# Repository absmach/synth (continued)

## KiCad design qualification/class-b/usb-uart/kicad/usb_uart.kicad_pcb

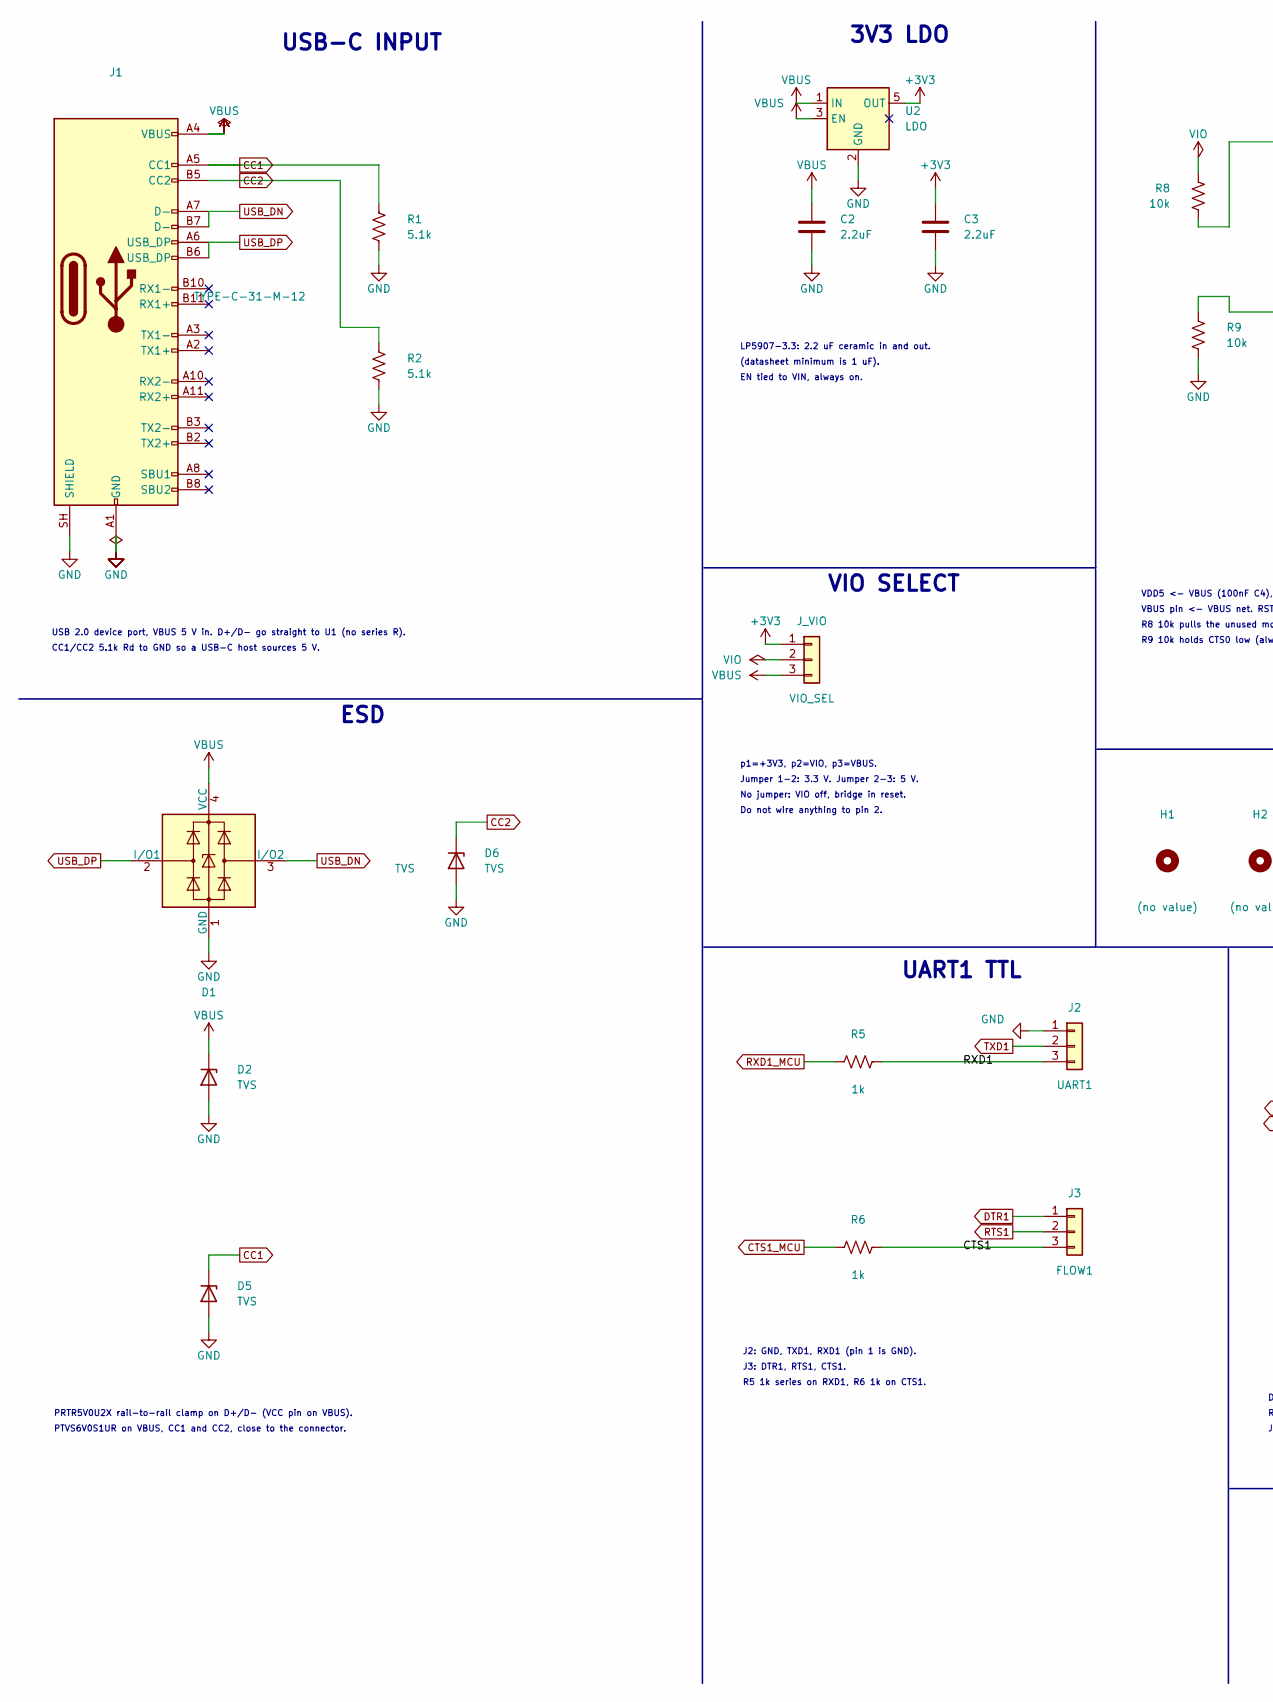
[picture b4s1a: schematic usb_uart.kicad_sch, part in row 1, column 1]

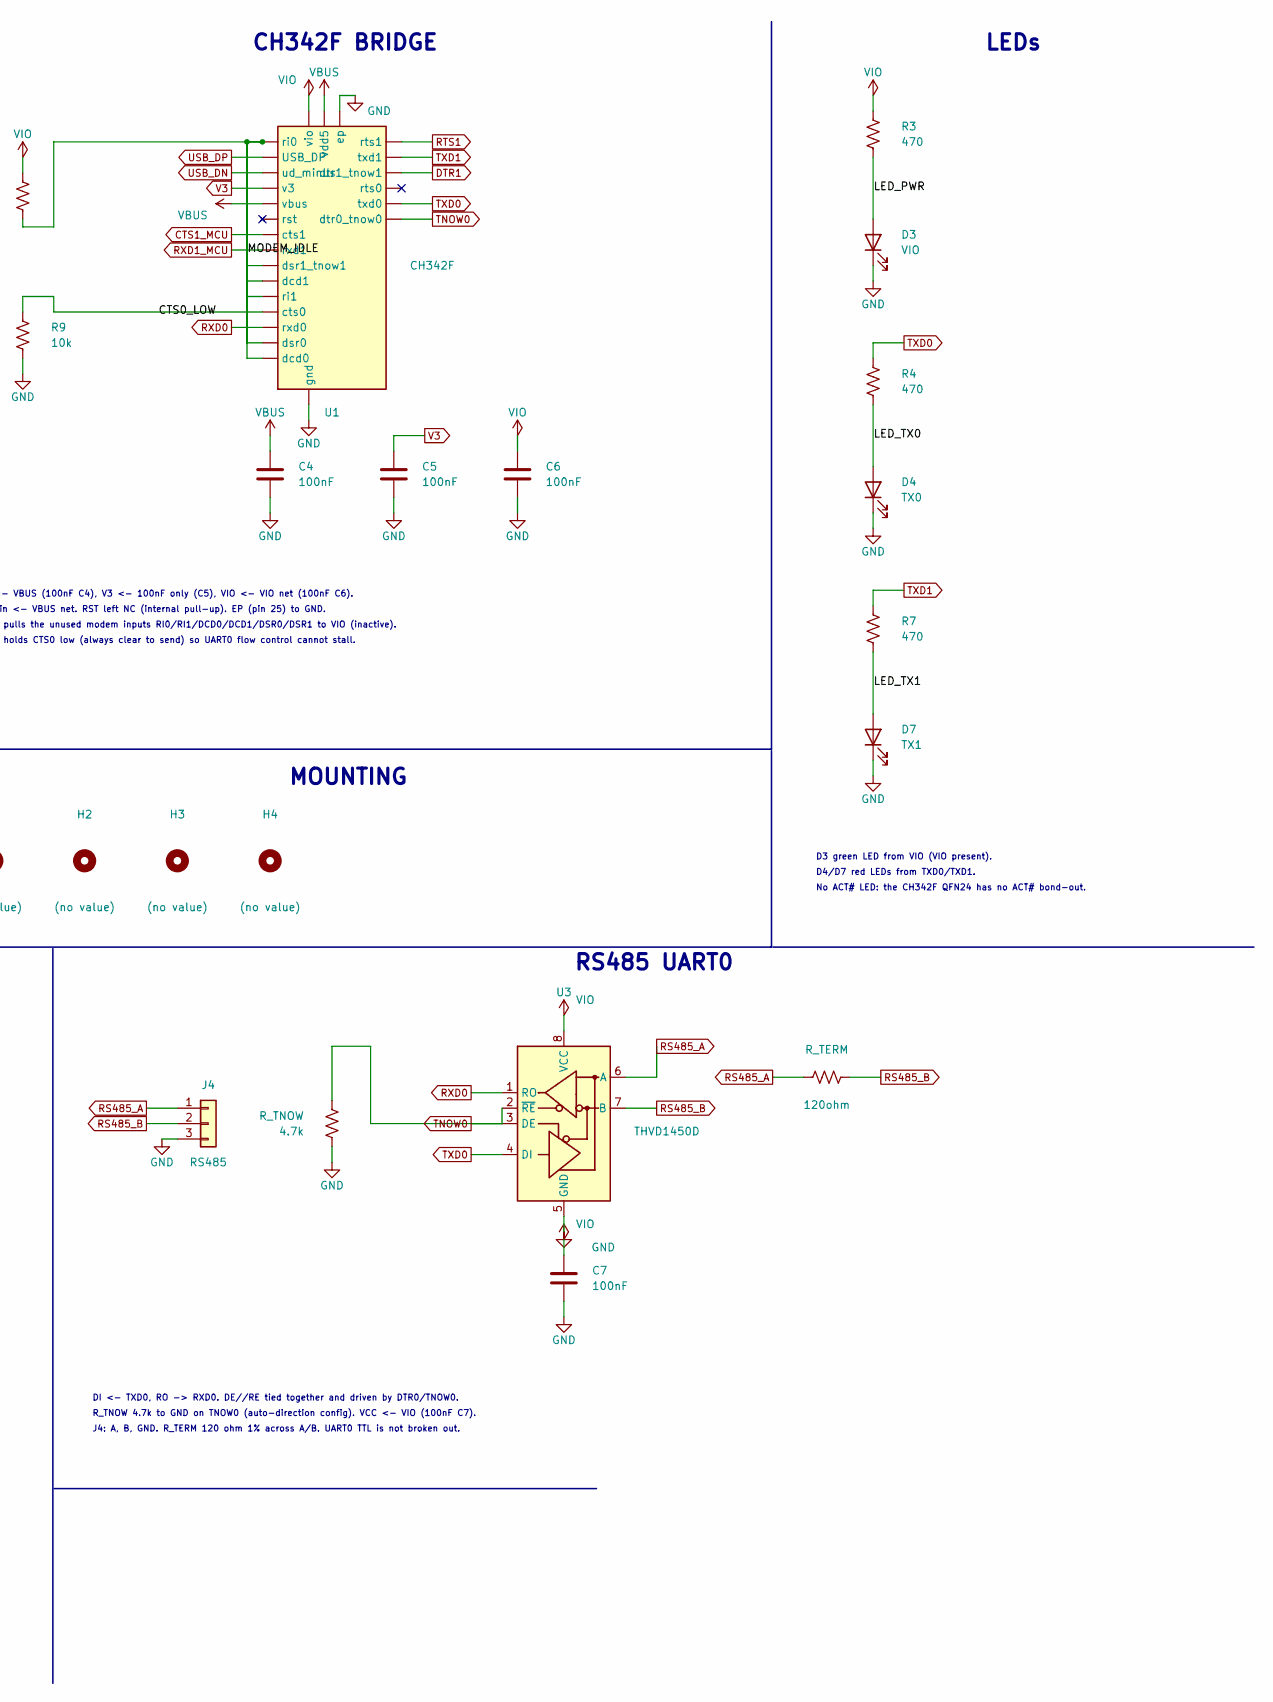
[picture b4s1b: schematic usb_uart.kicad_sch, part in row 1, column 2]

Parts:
C2, C3: 2.2uF; C_0603_1608Metric; Voltage 16V
C4, C5, C6, C7: 100nF; C_0603_1608Metric; Voltage 16V
D1: TVS; SOT-143; MPN PRTR5V0U2X
D2, D5, D6: TVS; Nexperia_CFP3_SOD-123W; MPN PTVS6V0S1UR
D3: VIO; LED_0603_1608Metric; MPN LTST-C190KGKT
D4: TX0; LED_0603_1608Metric; MPN LTST-C190KRKT
D7: TX1; LED_0603_1608Metric; MPN LTST-C190KRKT
H1, H2, H3, H4: (no value); MountingHole_2.5mm
J1: TYPE-C-31-M-12; USB_C_Receptacle_HRO_TYPE-C-31-M-12; MPN TYPE-C-31-M-12; LCSC C165948
J2: UART1; PinHeader_1x03_P2.54mm_Vertical
J3: FLOW1; PinHeader_1x03_P2.54mm_Vertical
J4: RS485; PinHeader_1x03_P2.54mm_Vertical
J_VIO: VIO_SEL; PinHeader_1x03_P2.54mm_Vertical
R1, R2: 5.1k; R_0603_1608Metric
R3, R4, R7: 470; R_0603_1608Metric
R5, R6: 1k; R_0603_1608Metric
R8, R9: 10k; R_0603_1608Metric
R_TERM: 120ohm; R_0603_1608Metric; Tolerance 1%
R_TNOW: 4.7k; R_0603_1608Metric; Tolerance 1%
U1: CH342F; QFN-24-1EP_4x4mm_P0.5mm_EP2.6x2.6mm; MPN CH342F; LCSC C2841530
U2: LDO; SOT-23-5; MPN LP5907MFX-3.3; LCSC C83437
U3: THVD1450D; SOIC-8_3.9x4.9mm_P1.27mm; MPN THVD1450D; LCSC C2671361

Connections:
+3V3: C3.1, J_VIO.1, U2.5 (OUT)
CC1: D5.1 (K), J1.A5 (CC1), R1.1
CC2: D6.1 (K), J1.B5 (CC2), R2.1
CTS0_LOW: R9.1, U1.18 (cts0)
CTS1: J3.3, R6.2
CTS1_MCU: R6.1, U1.10 (cts1)
DTR1: J3.1, U1.15 (dtr1_tnow1)
GND: C2.2, C3.2, C4.2, C5.2, C6.2, C7.2, D1.1 (GND), D2.2 (A), D3.1 (K), D4.1 (K), D5.2 (A), D6.2 (A), D7.1 (K), J1.A1 (GND), J1.A12 (GND), J1.B1 (GND), J1.B12 (GND), J1.SH (SHIELD), J2.1, J4.3, R1.2, R2.2, R9.2, R_TNOW.2, U1.2 (gnd), U1.25 (ep), U2.2 (GND), U3.5 (GND)
LED_PWR: D3.2 (A), R3.2
LED_TX0: D4.2 (A), R4.2
LED_TX1: D7.2 (A), R7.2
RS485_A: J4.1, R_TERM.1, U3.6 (A)
RS485_B: J4.2, R_TERM.2, U3.7 (B)
RTS1: J3.2, U1.11 (rts1)
RXD0: U1.20 (rxd0), U3.1 (RO)
RXD1: J2.3, R5.2
TNOW0: R_TNOW.1, U1.23 (dtr0_tnow0), U3.2 (~RE), U3.3 (DE)
TXD0: R4.1, U1.21 (txd0), U3.4 (DI)
TXD1: J2.2, R7.1, U1.13 (txd1)
USB_DN: D1.3 (I/O2), J1.A7 (D-), J1.B7 (D-), U1.4 (ud_minus)
USB_DP: D1.2 (I/O1), J1.A6 (D+), J1.B6 (D+), U1.3 (ud_plus)
V3: C5.1, U1.6 (v3)
VBUS: C2.1, C4.1, D1.4 (VCC), D2.1 (K), J1.A4 (VBUS), J1.A9 (VBUS), J1.B4 (VBUS), J1.B9 (VBUS), J_VIO.3, U1.7 (vdd5), U1.8 (vbus), U2.1 (IN), U2.3 (EN)
VIO: C6.1, C7.1, J_VIO.2, R3.1, R8.1, U1.5 (vio), U3.8 (VCC)

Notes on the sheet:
MOUNTING
USB-C INPUT
ESD
3V3 LDO
CH342F BRIDGE
VIO SELECT
UART1 TTL
RS485 UART0
LEDs
USB 2.0 device port, VBUS 5 V in. D+/D- go straight to U1 (no series R).
CC1/CC2 5.1k Rd to GND so a USB-C host sources 5 V.
PRTR5V0U2X rail-to-rail clamp on D+/D- (VCC pin on VBUS).
PTVS6V0S1UR on VBUS, CC1 and CC2, close to the connector.
LP5907-3.3: 2.2 uF ceramic in and out.
(datasheet minimum is 1 uF).
EN tied to VIN, always on.
VDD5 <- VBUS (100nF C4), V3 <- 100nF only (C5), VIO <- VIO net (100nF C6).
VBUS pin <- VBUS net. RST left NC (internal pull-up). EP (pin 25) to GND.
R8 10k pulls the unused modem inputs RI0/RI1/DCD0/DCD1/DSR0/DSR1 to VIO (inactive).
R9 10k holds CTS0 low (always clear to send) so UART0 flow control cannot stall.
p1=+3V3, p2=VIO, p3=VBUS.
Jumper 1-2: 3.3 V. Jumper 2-3: 5 V.
No jumper: VIO off, bridge in reset.
Do not wire anything to pin 2.
J2: GND, TXD1, RXD1 (pin 1 is GND).
J3: DTR1, RTS1, CTS1.
R5 1k series on RXD1, R6 1k on CTS1.
DI <- TXD0, RO -> RXD0. DE//RE tied together and driven by DTR0/TNOW0.
R_TNOW 4.7k to GND on TNOW0 (auto-direction config). VCC <- VIO (100nF C7).
J4: A, B, GND. R_TERM 120 ohm 1% across A/B. UART0 TTL is not broken out.
D3 green LED from VIO (VIO present).
D4/D7 red LEDs from TXD0/TXD1.
No ACT# LED: the CH342F QFN24 has no ACT# bond-out.

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
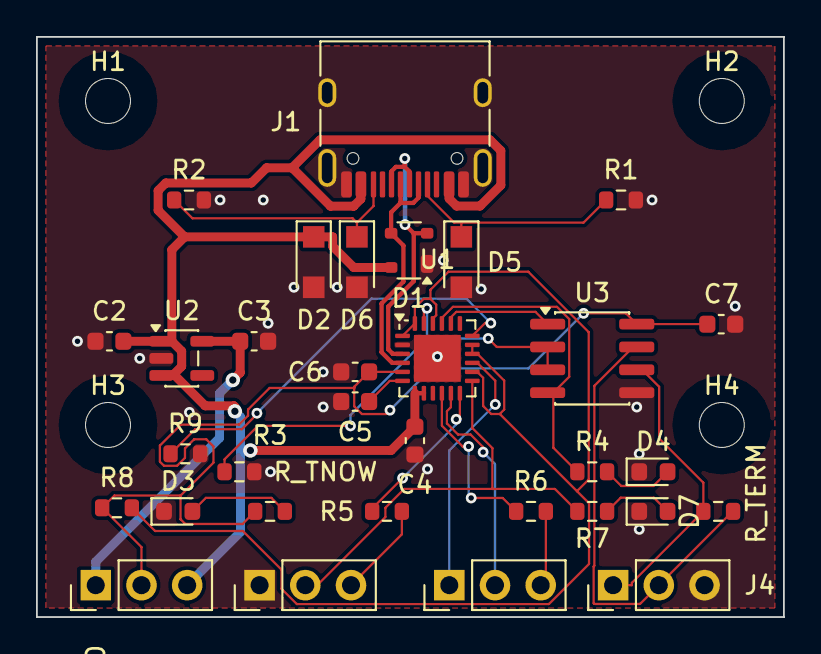
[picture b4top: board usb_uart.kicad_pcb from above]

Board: 2 copper layers, 41.5 x 32.2 mm, 36 parts (0 on the bottom side), 26 nets.

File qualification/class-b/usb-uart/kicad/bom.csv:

refdes,value,kind,description,kicad_symbol,kicad_footprint,lcsc_pn,mpn
C2,2.2uF,capacitor,"Generic 0603 MLCC, X7R/X5R, any value",Device:C,Capacitor_SMD:C_0603_1608Metric,,
C3,2.2uF,capacitor,"Generic 0603 MLCC, X7R/X5R, any value",Device:C,Capacitor_SMD:C_0603_1608Metric,,
C4,100nF,capacitor,"Generic 0603 MLCC, X7R/X5R, any value",Device:C,Capacitor_SMD:C_0603_1608Metric,,
C5,100nF,capacitor,"Generic 0603 MLCC, X7R/X5R, any value",Device:C,Capacitor_SMD:C_0603_1608Metric,,
C6,100nF,capacitor,"Generic 0603 MLCC, X7R/X5R, any value",Device:C,Capacitor_SMD:C_0603_1608Metric,,
C7,100nF,capacitor,"Generic 0603 MLCC, X7R/X5R, any value",Device:C,Capacitor_SMD:C_0603_1608Metric,,
D1,TVS,diode,"Nexperia PRTR5V0U2X ultra low capacitance (1 pF) 2-line rail-to-rail ESD protection for USB 2.0 data lines, SOT143B",Power_Protection:PRTR5V0U2X,Package_TO_SOT_SMD:SOT-143,,PRTR5V0U2X
D2,TVS,diode,"Nexperia PTVS6V0S1UR 400 W unidirectional TVS, 6.0 V standoff, SOD123W, for VBUS and CC",Device:D_Zener,Diode_SMD:Nexperia_CFP3_SOD-123W,,PTVS6V0S1UR
D3,VIO,led,"Lite-On LTST-C190KGKT green AlInGaP LED, 0603, Vf 1.9 to 2.4V at 20mA",Device:LED,LED_SMD:LED_0603_1608Metric,,LTST-C190KGKT
D4,TX0,led,"Lite-On LTST-C190KRKT red AlInGaP LED, 0603, Vf 1.6 to 2.4V at 20mA",Device:LED,LED_SMD:LED_0603_1608Metric,,LTST-C190KRKT
D5,TVS,diode,"Nexperia PTVS6V0S1UR 400 W unidirectional TVS, 6.0 V standoff, SOD123W, for VBUS and CC",Device:D_Zener,Diode_SMD:Nexperia_CFP3_SOD-123W,,PTVS6V0S1UR
D6,TVS,diode,"Nexperia PTVS6V0S1UR 400 W unidirectional TVS, 6.0 V standoff, SOD123W, for VBUS and CC",Device:D_Zener,Diode_SMD:Nexperia_CFP3_SOD-123W,,PTVS6V0S1UR
D7,TX1,led,"Lite-On LTST-C190KRKT red AlInGaP LED, 0603, Vf 1.6 to 2.4V at 20mA",Device:LED,LED_SMD:LED_0603_1608Metric,,LTST-C190KRKT
H1,(no value),mounting_hole,M2.5 non-plated mounting hole (NPTH) for a board corner,Mechanical:MountingHole,MountingHole:MountingHole_2.5mm,,
H2,(no value),mounting_hole,M2.5 non-plated mounting hole (NPTH) for a board corner,Mechanical:MountingHole,MountingHole:MountingHole_2.5mm,,
H3,(no value),mounting_hole,M2.5 non-plated mounting hole (NPTH) for a board corner,Mechanical:MountingHole,MountingHole:MountingHole_2.5mm,,
H4,(no value),mounting_hole,M2.5 non-plated mounting hole (NPTH) for a board corner,Mechanical:MountingHole,MountingHole:MountingHole_2.5mm,,
J1,TYPE-C-31-M-12,connector,"USB-C receptacle, 24-pin SMD. Modelled here with primary and mirrored power/ground/data pins for full pad coverage.",Connector:USB_C_Receptacle,Connector_USB:USB_C_Receptacle_HRO_TYPE-C-31-M-12,C165948,TYPE-C-31-M-12
J2,UART1,connector,"1x3 through-hole pin header, 2.54mm pitch",Connector_Generic:Conn_01x03,Connector_PinHeader_2.54mm:PinHeader_1x03_P2.54mm_Vertical,,
J3,FLOW1,connector,"1x3 through-hole pin header, 2.54mm pitch",Connector_Generic:Conn_01x03,Connector_PinHeader_2.54mm:PinHeader_1x03_P2.54mm_Vertical,,
J4,RS485,connector,"1x3 through-hole pin header, 2.54mm pitch",Connector_Generic:Conn_01x03,Connector_PinHeader_2.54mm:PinHeader_1x03_P2.54mm_Vertical,,
J_VIO,VIO_SEL,connector,"1x3 through-hole pin header, 2.54mm pitch",Connector_Generic:Conn_01x03,Connector_PinHeader_2.54mm:PinHeader_1x03_P2.54mm_Vertical,,
R1,5.1k,resistor,"Generic 0603 thick-film resistor, any value",Device:R_US,Resistor_SMD:R_0603_1608Metric,,
R2,5.1k,resistor,"Generic 0603 thick-film resistor, any value",Device:R_US,Resistor_SMD:R_0603_1608Metric,,
R3,470,resistor,"Generic 0603 thick-film resistor, any value",Device:R_US,Resistor_SMD:R_0603_1608Metric,,
R4,470,resistor,"Generic 0603 thick-film resistor, any value",Device:R_US,Resistor_SMD:R_0603_1608Metric,,
R5,1k,resistor,"Generic 0603 thick-film resistor, any value",Device:R_US,Resistor_SMD:R_0603_1608Metric,,
R6,1k,resistor,"Generic 0603 thick-film resistor, any value",Device:R_US,Resistor_SMD:R_0603_1608Metric,,
R7,470,resistor,"Generic 0603 thick-film resistor, any value",Device:R_US,Resistor_SMD:R_0603_1608Metric,,
R8,10k,resistor,"Generic 0603 thick-film resistor, any value",Device:R_US,Resistor_SMD:R_0603_1608Metric,,
R9,10k,resistor,"Generic 0603 thick-film resistor, any value",Device:R_US,Resistor_SMD:R_0603_1608Metric,,
R_TERM,120ohm,resistor,"Generic 0603 thick-film resistor, any value",Device:R_US,Resistor_SMD:R_0603_1608Metric,,
R_TNOW,4.7k,resistor,"Generic 0603 thick-film resistor, any value",Device:R_US,Resistor_SMD:R_0603_1608Metric,,
U1,CH342F,ic,"WCH CH342F USB to dual UART bridge controller, QFN-24 (4x4 mm, 0.5 mm pitch, exposed pad)",,Package_DFN_QFN:QFN-24-1EP_4x4mm_P0.5mm_EP2.6x2.6mm,C2841530,CH342F
U2,LDO,regulator,"TI LP5907 3.3V low-noise LDO, 250mA, SOT-23-5",Regulator_Linear:LP5907MFX-3.3,Package_TO_SOT_SMD:SOT-23-5,C83437,LP5907MFX-3.3
U3,THVD1450D,ic,"TI THVD1450D RS-485 transceiver, 3.3-5 V, 50 Mbps, ±18 kV IEC 61000-4-2 contact ESD, SOIC-8",Interface_UART:THVD1450D,Package_SO:SOIC-8_3.9x4.9mm_P1.27mm,C2671361,THVD1450D

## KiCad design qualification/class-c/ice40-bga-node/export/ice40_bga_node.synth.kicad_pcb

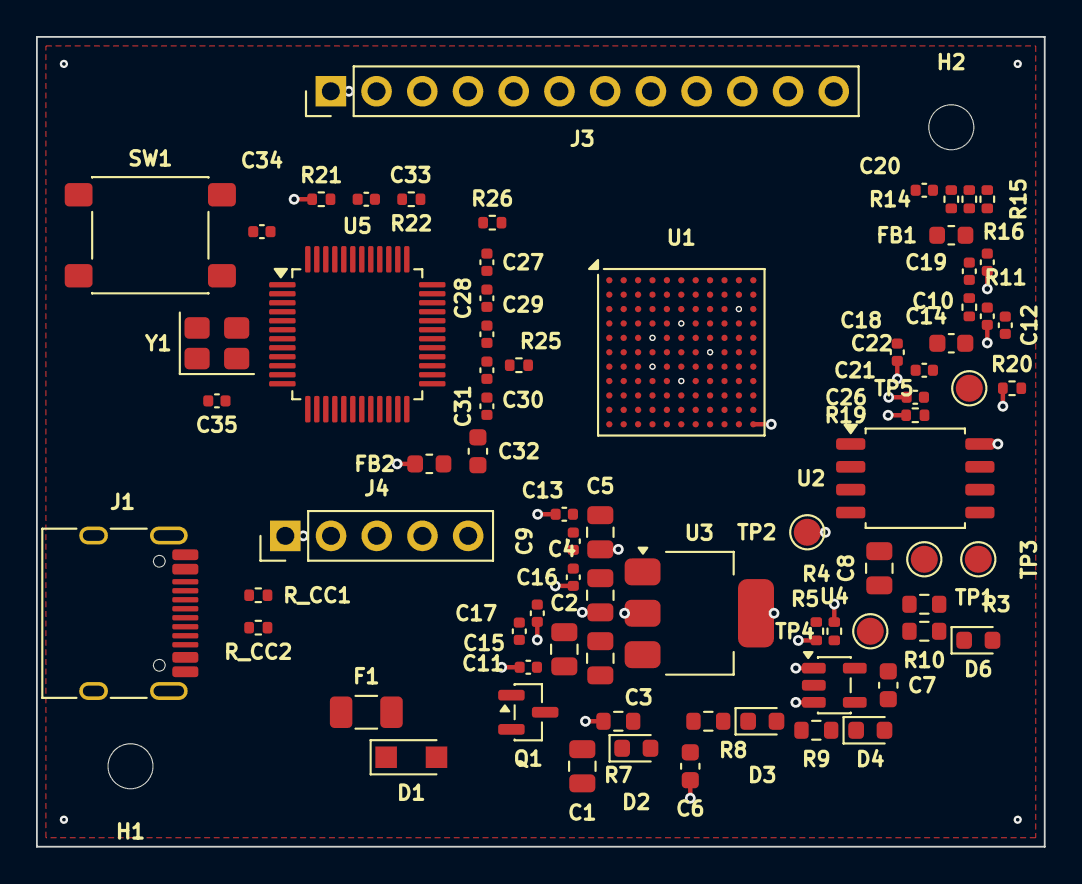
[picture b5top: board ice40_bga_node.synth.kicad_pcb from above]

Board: 6 copper layers, 56.0 x 45.0 mm, 77 parts (0 on the bottom side), 42 nets.

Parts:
C1, C2, C3, C4, C5: 10uF; C_0805_2012Metric
C6, C7, C22: 1uF; C_0603_1608Metric
C8: 4.7uF; C_0805_2012Metric
C9, C10, C11, C12, C13, C14, C15, C16, C17, C18, C19, C20, C21, C26, C27, C28, C29, C30, C31, C33: 100nF; C_0402_1005Metric
C32: 4.7uF; C_0603_1608Metric
C34, C35: 10pF; C_0402_1005Metric
D1: PTVS6V0S1UR; Nexperia_CFP3_SOD-123W
D2: 0603-GREEN; LED_0603_1608Metric
D3: (no value); LED_0603_1608Metric
D4, D6: 0603-RED; LED_0603_1608Metric
F1: MF-NSMF050-2; Fuse_1206_3216Metric
FB1, FB2: (no value); L_0603_1608Metric
H1, H2: (no value); MountingHole_2.5mm
J1: TYPE-C-31-M-12; USB_C_Receptacle_HRO_TYPE-C-31-M-12
J3: (no value); PinHeader_1x12_P2.54mm_Vertical
J4: (no value); PinHeader_1x05_P2.54mm_Vertical
Q1: SI2301CDS-T1-GE3; SOT-23
R3: 100k; R_0603_1608Metric
R4, R5, R19, R20, R21, R22: 10k; R_0402_1005Metric
R7, R8, R9, R10: 1k; R_0603_1608Metric
R11, R14, R15, R16: 100; R_0402_1005Metric
R25, R26: 22; R_0402_1005Metric
R_CC1, R_CC2: 5.1k; R_0402_1005Metric
SW1: PTS645SM43SMTR92 LFS; SW_SPST_PTS645Sx43SMTR92
TP1, TP2, TP3, TP4, TP5: (no value); TestPoint_Pad_D1.5mm
U1: ICE40HX4K-BG121; BGA-121_9.0x9.0mm_Layout11x11_P0.8mm_Ball0.4mm_Pad0.35mm_NS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
U2: W25Q128JVSIQ; SOIC-8_5.3x5.3mm_P1.27mm
U3: AMS1117-3.3; SOT-223-3_TabPin2
U4: TLV70012-1.2; TSOT-23-5
U5: STM32F103C8T6; LQFP-48_7x7mm_P0.5mm
Y1: 3TJ480000FYLBC; Crystal_SMD_3225-4Pin_3.2x2.5mm

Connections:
+1V2: C7.1, C8.1, C9.1, C10.1, C11.1, C12.1, FB1.1, TP3.1, U1.D4, U1.D8, U1.H4, U1.H8, U4.5
+3V3: C4.1, C5.1, C6.1, C13.1, C14.1, C15.1, C16.1, C17.1, C18.1, C19.1, C26.1, FB2.1, J3.1, J4.1, R4.1, R5.2, R7.1, R19.1, R20.1, R21.1, TP2.1, U1.B10, U1.C10, U1.D6, U1.E4, U1.F8, U1.G4, U1.H6, U1.L11, U2.8, U3.2, U4.1, U4.3
+3V3_MCU: C27.1, C28.1, C29.1, C30.1, C31.1, C32.1, FB2.2, U5.1, U5.9, U5.24, U5.36, U5.48
+5V: C1.1, C2.1, C3.1, Q1.2, TP1.1, U3.3
BOOT0: R22.1, U5.44
CDONE: R4.2, R8.1, TP5.1, U1.K8, U5.19
CFG_SCK: U1.L10, U2.6, U5.15
CFG_SDI: U1.J9, U2.2, U5.16
CFG_SDO: U1.K9, U2.5, U5.17
CFG_SS_B: R20.2, U1.K10, U2.1, U5.14
CRESET_B: R5.1, TP4.1, U1.L9, U5.18
FA1: R11.1, U1.A1, U1.B1
FA4: R14.1, U1.A4, U1.A9, U1.B4, U1.B9
FA5: R15.1, U1.A5
FA6: R16.1, U1.A6, U1.B6
FLASH_WPHOLD: R19.2, U2.3, U2.7
GND: C1.2, C2.2, C3.2, C4.2, C5.2, C6.2, C7.2, C8.2, C9.2, C10.2, C11.2, C12.2, C13.2, C14.2, C15.2, C16.2, C17.2, C18.2, C19.2, C20.2, C21.2, C22.2, C26.2, C27.2, C28.2, C29.2, C30.2, C31.2, C32.2, C33.2, C34.2, C35.2, D1.2, D2.1, D3.1, D4.1, D6.1, J1.A1, J1.A12, J1.B1, J1.B12, J1.SH, J3.2, J4.5, R3.2, R22.2, R_CC1.2, R_CC2.2, SW1.2, U1.C5, U1.E5, U1.E6, U1.E7, U1.F5, U1.F6, U1.F7, U1.G5, U1.G6, U1.G7, U1.H5, U1.L6, U2.4, U3.1, U4.2, U5.8, U5.23, U5.35, U5.47, Y1.2, Y1.4
HA1: J3.5, R11.2
HA4: J3.8, R14.2
HA5: J3.9, R15.2
HA6: J3.10, R16.2
HSE_IN: C34.1, U5.5, Y1.1
HSE_OUT: C35.1, U5.6, Y1.3
LED_CDONE: D3.2, R8.2
LED_PWR: D2.2, R7.2
LED_U1: D4.2, R9.2
LED_U1_R: R9.1, U1.L4
LED_U2: D6.2, R10.2
LED_U2_R: R10.1, U1.L3
NRST: C33.1, J4.4, R21.2, SW1.1, U5.7
Q1_GATE: Q1.1, R3.1
SWCLK: J4.3, U5.37
SWDIO: J4.2, U5.34
USB_CC1: J1.A5, R_CC1.1
USB_CC2: J1.B5, R_CC2.1
USB_DM: R26.2, U5.32
USB_DM_C: J1.A7, J1.B7, R26.1
USB_DP: R25.2, U5.33
USB_DP_C: J1.A6, J1.B6, R25.1
VBUS: F1.1, J1.A4, J1.A9, J1.B4, J1.B9
VBUS_F: D1.1, F1.2, Q1.3
VCCPLL: C20.1, C21.1, C22.1, FB1.2, U1.C6, U1.J6

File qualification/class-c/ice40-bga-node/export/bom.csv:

refdes,value,kind,description,kicad_symbol,kicad_footprint,lcsc_pn,mpn
C1,10uF,capacitor,"Generic 0805 MLCC, X7R/X5R, any value",Device:C,Capacitor_SMD:C_0805_2012Metric,,
C10,100nF,capacitor,"Generic 0402 MLCC, X7R/X5R, any value",Device:C,Capacitor_SMD:C_0402_1005Metric,,
C11,100nF,capacitor,"Generic 0402 MLCC, X7R/X5R, any value",Device:C,Capacitor_SMD:C_0402_1005Metric,,
C12,100nF,capacitor,"Generic 0402 MLCC, X7R/X5R, any value",Device:C,Capacitor_SMD:C_0402_1005Metric,,
C13,100nF,capacitor,"Generic 0402 MLCC, X7R/X5R, any value",Device:C,Capacitor_SMD:C_0402_1005Metric,,
C14,100nF,capacitor,"Generic 0402 MLCC, X7R/X5R, any value",Device:C,Capacitor_SMD:C_0402_1005Metric,,
C15,100nF,capacitor,"Generic 0402 MLCC, X7R/X5R, any value",Device:C,Capacitor_SMD:C_0402_1005Metric,,
C16,100nF,capacitor,"Generic 0402 MLCC, X7R/X5R, any value",Device:C,Capacitor_SMD:C_0402_1005Metric,,
C17,100nF,capacitor,"Generic 0402 MLCC, X7R/X5R, any value",Device:C,Capacitor_SMD:C_0402_1005Metric,,
C18,100nF,capacitor,"Generic 0402 MLCC, X7R/X5R, any value",Device:C,Capacitor_SMD:C_0402_1005Metric,,
C19,100nF,capacitor,"Generic 0402 MLCC, X7R/X5R, any value",Device:C,Capacitor_SMD:C_0402_1005Metric,,
C2,10uF,capacitor,"Generic 0805 MLCC, X7R/X5R, any value",Device:C,Capacitor_SMD:C_0805_2012Metric,,
C20,100nF,capacitor,"Generic 0402 MLCC, X7R/X5R, any value",Device:C,Capacitor_SMD:C_0402_1005Metric,,
C21,100nF,capacitor,"Generic 0402 MLCC, X7R/X5R, any value",Device:C,Capacitor_SMD:C_0402_1005Metric,,
C22,1uF,capacitor,"Generic 0603 MLCC, X7R/X5R, any value",Device:C,Capacitor_SMD:C_0603_1608Metric,,
C26,100nF,capacitor,"Generic 0402 MLCC, X7R/X5R, any value",Device:C,Capacitor_SMD:C_0402_1005Metric,,
C3,10uF,capacitor,"Generic 0805 MLCC, X7R/X5R, any value",Device:C,Capacitor_SMD:C_0805_2012Metric,,
C4,10uF,capacitor,"Generic 0805 MLCC, X7R/X5R, any value",Device:C,Capacitor_SMD:C_0805_2012Metric,,
C5,10uF,capacitor,"Generic 0805 MLCC, X7R/X5R, any value",Device:C,Capacitor_SMD:C_0805_2012Metric,,
C6,1uF,capacitor,"Generic 0603 MLCC, X7R/X5R, any value",Device:C,Capacitor_SMD:C_0603_1608Metric,,
C7,1uF,capacitor,"Generic 0603 MLCC, X7R/X5R, any value",Device:C,Capacitor_SMD:C_0603_1608Metric,,
C8,4.7uF,capacitor,"Generic 0805 MLCC, X7R/X5R, any value",Device:C,Capacitor_SMD:C_0805_2012Metric,,
C9,100nF,capacitor,"Generic 0402 MLCC, X7R/X5R, any value",Device:C,Capacitor_SMD:C_0402_1005Metric,,
D1,PTVS6V0S1UR,diode,"Nexperia PTVS6V0S1UR 400 W unidirectional TVS, 6.0 V standoff, SOD123W, for VBUS and CC",Device:D_Zener,Diode_SMD:Nexperia_CFP3_SOD-123W,,PTVS6V0S1UR
D2,0603-GREEN,led,"Green LED, 0603 package, ~2.2V Vf",Device:LED,LED_SMD:LED_0603_1608Metric,C72043,0603-GREEN
D3,(no value),led,"Amber surface-mount LED, 0603",Device:LED,LED_SMD:LED_0603_1608Metric,,
D4,0603-RED,led,"Red LED, 0603 package, ~2.0V Vf",Device:LED,LED_SMD:LED_0603_1608Metric,C2286,0603-RED
D6,0603-RED,led,"Red LED, 0603 package, ~2.0V Vf",Device:LED,LED_SMD:LED_0603_1608Metric,C2286,0603-RED
F1,MF-NSMF050-2,fuse,"Bourns MF-NSMF050-2 resettable fuse, 0.5 A hold, 13.2 V, 1206",Device:Polyfuse,Fuse:Fuse_1206_3216Metric,C75464,MF-NSMF050-2
FB1,(no value),inductor,"0603 ferrite bead, 600Ω @ 100MHz — EMI suppression",Device:FerriteBead,Inductor_SMD:L_0603_1608Metric,,
H1,(no value),mounting_hole,M2.5 non-plated mounting hole (NPTH) for a board corner,Mechanical:MountingHole,MountingHole:MountingHole_2.5mm,,
H2,(no value),mounting_hole,M2.5 non-plated mounting hole (NPTH) for a board corner,Mechanical:MountingHole,MountingHole:MountingHole_2.5mm,,
J1,HX PZ2.54-1x2P ZZ,connector,"1x2 through-hole pin header, 2.54mm pitch, for a jumper",Connector_Generic:Conn_01x02,Connector_PinHeader_2.54mm:PinHeader_1x02_P2.54mm_Vertical,C32713268,HX PZ2.54-1x2P ZZ
J3,(no value),connector,"1x12 through-hole pin header, 2.54 mm pitch (GPIO); datasheet_url is the product page of the Harwin M20 series, no manufacturer PDF link was verifiable",Connector_Generic:Conn_01x12,Connector_PinHeader_2.54mm:PinHeader_1x12_P2.54mm_Vertical,,
Q1,SI2301CDS-T1-GE3,transistor,"Vishay Si2301 P-channel power MOSFET, SOT-23",Transistor_FET:Si2301CDS,Package_TO_SOT_SMD:SOT-23,C10487,SI2301CDS-T1-GE3
R10,1k,resistor,"Generic 0603 thick-film resistor, any value",Device:R_US,Resistor_SMD:R_0603_1608Metric,,
R11,100,resistor,"Generic 0402 thick-film resistor, any value",Device:R_US,Resistor_SMD:R_0402_1005Metric,,
R14,100,resistor,"Generic 0402 thick-film resistor, any value",Device:R_US,Resistor_SMD:R_0402_1005Metric,,
R15,100,resistor,"Generic 0402 thick-film resistor, any value",Device:R_US,Resistor_SMD:R_0402_1005Metric,,
R16,100,resistor,"Generic 0402 thick-film resistor, any value",Device:R_US,Resistor_SMD:R_0402_1005Metric,,
R19,10k,resistor,"Generic 0402 thick-film resistor, any value",Device:R_US,Resistor_SMD:R_0402_1005Metric,,
R20,10k,resistor,"Generic 0402 thick-film resistor, any value",Device:R_US,Resistor_SMD:R_0402_1005Metric,,
R3,100k,resistor,"Generic 0603 thick-film resistor, any value",Device:R_US,Resistor_SMD:R_0603_1608Metric,,
R4,10k,resistor,"Generic 0402 thick-film resistor, any value",Device:R_US,Resistor_SMD:R_0402_1005Metric,,
R5,10k,resistor,"Generic 0402 thick-film resistor, any value",Device:R_US,Resistor_SMD:R_0402_1005Metric,,
R7,1k,resistor,"Generic 0603 thick-film resistor, any value",Device:R_US,Resistor_SMD:R_0603_1608Metric,,
R8,1k,resistor,"Generic 0603 thick-film resistor, any value",Device:R_US,Resistor_SMD:R_0603_1608Metric,,
R9,1k,resistor,"Generic 0603 thick-film resistor, any value",Device:R_US,Resistor_SMD:R_0603_1608Metric,,
TP1,(no value),testpoint,"SMD test point pad, 1.5 mm — probe point for a net",Connector:TestPoint,TestPoint:TestPoint_Pad_D1.5mm,,
TP2,(no value),testpoint,"SMD test point pad, 1.5 mm — probe point for a net",Connector:TestPoint,TestPoint:TestPoint_Pad_D1.5mm,,
TP3,(no value),testpoint,"SMD test point pad, 1.5 mm — probe point for a net",Connector:TestPoint,TestPoint:TestPoint_Pad_D1.5mm,,
TP4,(no value),testpoint,"SMD test point pad, 1.5 mm — probe point for a net",Connector:TestPoint,TestPoint:TestPoint_Pad_D1.5mm,,
TP5,(no value),testpoint,"SMD test point pad, 1.5 mm — probe point for a net",Connector:TestPoint,TestPoint:TestPoint_Pad_D1.5mm,,
U1,ICE40HX4K-BG121,fpga,"Lattice iCE40 HX4K FPGA, 121-ball 0.8mm BGA. Copy of registry part ice40hx4k_bg121 with exactly one change: vpp_fast (B10) is a passive pin that is not required, so it can be left unconnected.",FPGA_Lattice:ICE40HX4K-BG121,Package_BGA:BGA-121_9.0x9.0mm_Layout11x11_P0.8mm_Ball0.4mm_Pad0.35mm_NSMD,,ICE40HX4K-BG121
U2,W25Q128JVSIQ,memory,"Winbond W25Q128JVSIQ 128Mbit SPI NOR flash, SOIC-8 208 mil (5.3 mm body, 7.7 mm lead span, 1.27 mm pitch)",Memory_Flash:W25Q128JVS,Package_SO:SOIC-8_5.3x5.3mm_P1.27mm,C97521,W25Q128JVSIQ
U3,AMS1117-3.3,regulator,"AMS1117-3.3 fixed 3.3V LDO regulator, SOT-223 — common JLC stock",Regulator_Linear:AMS1117-3.3,Package_TO_SOT_SMD:SOT-223-3_TabPin2,C6186,AMS1117-3.3
U4,TLV70012-1.2,regulator,"TI TLV70012 1.2 V fixed LDO, 200 mA, 2.0 to 5.5 V input, SOT-23-THIN (DDC, TSOT-23-5). Pinout 1 IN, 2 GND, 3 EN, 4 NC, 5 OUT per TI TLV700xx datasheet SLVSA00; 1 uF input and output capacitors.",Regulator_Linear:TLV70012_SOT23-5,Package_TO_SOT_SMD:TSOT-23-5,,TLV70012DDCR

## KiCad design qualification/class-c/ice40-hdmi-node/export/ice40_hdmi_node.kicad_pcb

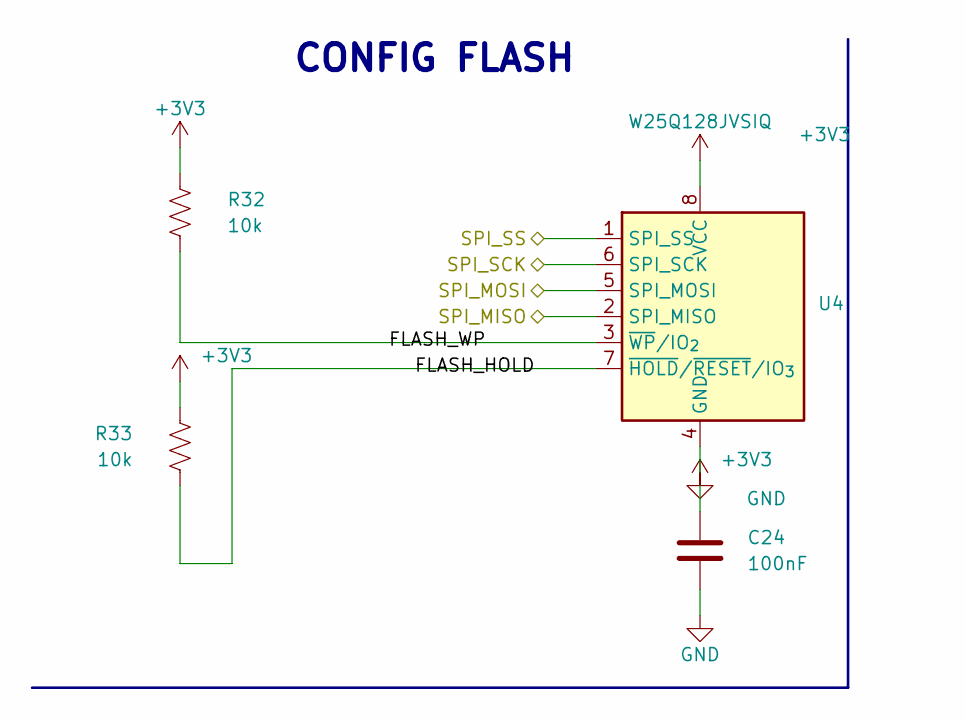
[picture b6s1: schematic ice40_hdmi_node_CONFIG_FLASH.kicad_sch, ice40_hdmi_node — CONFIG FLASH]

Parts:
C24: 100nF; C_0402_1005Metric
R32, R33: 10k; R_0603_1608Metric
U4: W25Q128JVSIQ; SOIC-8_5.3x5.3mm_P1.27mm; MPN W25Q128JVSIQ; LCSC C97521

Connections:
+3V3: C24.1, R32.1, R33.1, U4.8 (VCC); also elsewhere on the board
FLASH_HOLD: R33.2, U4.7 (~HOLD/~RESET/IO_{3})
FLASH_WP: R32.2, U4.3 (~WP/IO_{2})
GND: C24.2, U4.4 (GND); also elsewhere on the board
SPI_MISO: U4.2 (DO/IO_{1}); also elsewhere on the board
SPI_MOSI: U4.5 (DI/IO_{0}); also elsewhere on the board
SPI_SCK: U4.6 (CLK); also elsewhere on the board
SPI_SS: U4.1 (~CS); also elsewhere on the board

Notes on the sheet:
CONFIG FLASH
